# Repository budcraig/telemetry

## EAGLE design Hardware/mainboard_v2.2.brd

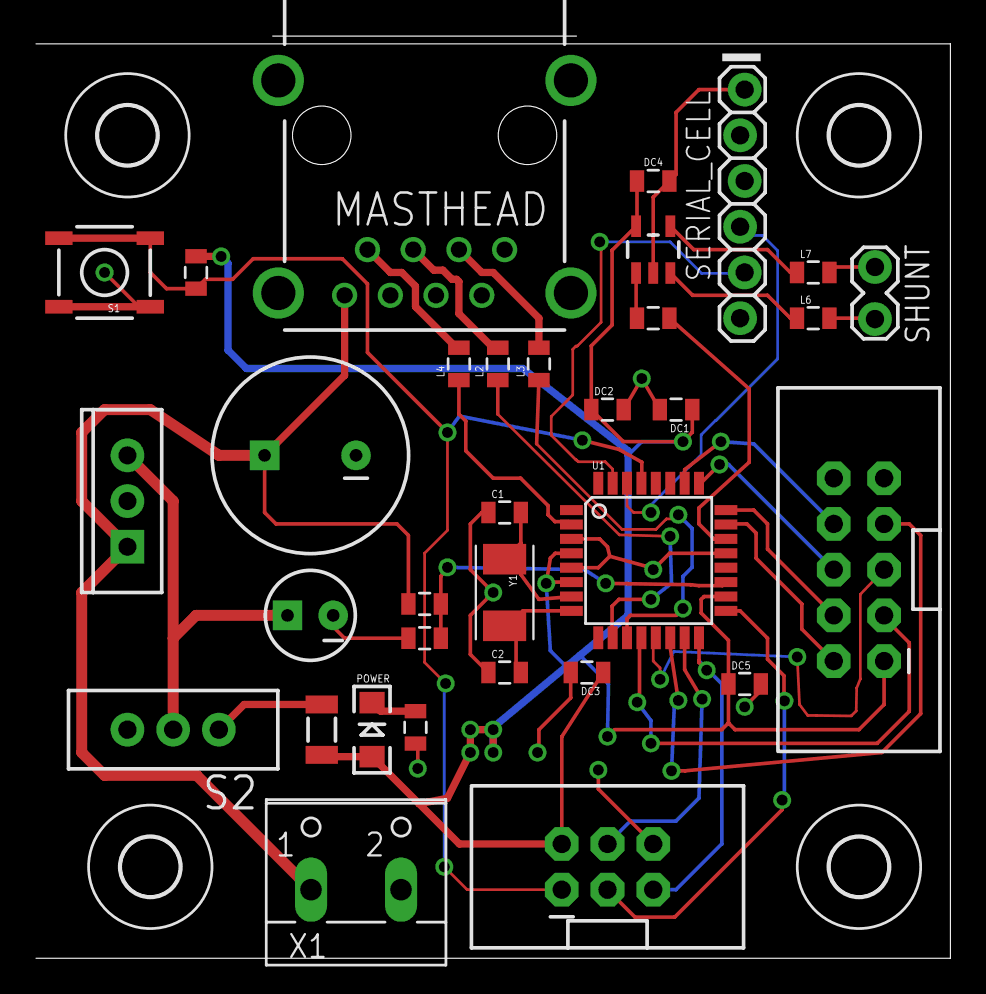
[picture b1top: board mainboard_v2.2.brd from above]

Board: 2 copper layers, 50.8 x 51.2 mm, 38 parts (1 on the bottom side), 34 nets.

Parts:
C1, C2: 22pF; 0805
C9: 100uF; CPOL-RADIAL-1000UF-25V
C10: 10uF; CPOL-RADIAL-10UF-25V
DC1, DC2, DC3, DC4, DC5: 0.1uF; 0805
H1, H2, H3, H4: MOUNT-HOLE3.2; 3,2
IC1: TO220-IGO
ICSP: 2X3-SHROUDED
L2, L3, L4, L6, L7: 0805
LCD: M05X2SHD_LOCK; 2X5-SHROUDED_LOCK
LOGO2: OSHW-LOGOL; OSHW-LOGO-L
MASTHEAD: RJ45-8L21-B; RJ45-SHIELD1
POWER: LED-1206
PTC: 750mA; PTC-1206
R1: 10kΩ; 0805
R2: 10kΩ 0.1%; 0805
R3: 1.2kΩ 0.1%; 0805
R4: 44.2kΩ 0.1%; 0805
R7: 56Ω; 0805
S1: TACTILE_SWITCH_SMD
S2: SWITCH-SPDT
SERIAL_CELL: 1X06_LOCK
SHUNT: 1X02_LOCK
U1: ATMEGA328P; TQFP32-08
U2: INA169; SOT23-5
X1: W237-102
Y1: CRYSTAL-TXC-7A

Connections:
3.3V: DC1.1, DC2.1, DC3.1, DC4.1, DC5.1, ICSP.2, LCD.1, POWER.A, PTC.2, R1.2, U1.4, U1.6, U1.18, U2.5
ANEM_CLK: L4.2, MASTHEAD.7
DIR_POT: L3.2, MASTHEAD.3
GND: C1.1, C2.1, C9.2, C10.2, DC1.2, DC2.2, DC3.2, DC4.2, DC5.2, IC1.GND, ICSP.6, LCD.9, MASTHEAD.1, MASTHEAD.2, MASTHEAD.4, MASTHEAD.6, R3.1, R7.1, S1.1, S1.2, SERIAL_CELL.1, U1.3, U1.5, U1.21, U2.2, X1.2
LCD_D4: LCD.2, U1.23
LCD_D5: LCD.4, U1.24
LCD_D6: LCD.6, U1.25
LCD_D7: LCD.8, U1.26
LCD_E: LCD.7, U1.14
LCD_RS: LCD.3, U1.12
LCD_RW: LCD.5, U1.13
MISO: ICSP.5, U1.16
MOSI: ICSP.4, U1.15
unnamed: PTC.1, S2.1
unnamed: L3.1, U1.11
unnamed: L2.1, U1.10
unnamed: L4.1, U1.2
unnamed: L6.1, U2.3
unnamed: L7.1, U2.4
unnamed: R4.2, U2.1
unnamed: POWER.C, R7.2
RESET: ICSP.1, R1.1, S1.3, S1.4, U1.29
SCK: ICSP.3, U1.17
SHIPS_BATTERY_VOLTAGE_ADC: R2.1, R3.2, U1.19
SHUNT: R4.1, U1.22
SHUNT+: L7.2, SHUNT.2
SHUNT-: L6.2, SHUNT.1
TEMP: L2.2, MASTHEAD.5
URX: SERIAL_CELL.4, U1.30
UTX: SERIAL_CELL.5, U1.31
VCC: C9.1, IC1.IN, MASTHEAD.8, R2.2, X1.1
VREG_OUT: C10.1, IC1.OUT, S2.2
XTAL1: C1.2, U1.7, Y1.P$2
XTAL2: C2.2, U1.8, Y1.P$1

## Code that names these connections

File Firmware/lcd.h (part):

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#define LCD_DATA1_PIN    1            /**< pin for 4bit data bit 1  */
#define LCD_DATA2_PIN    2            /**< pin for 4bit data bit 2  */
#define LCD_DATA3_PIN    3            /**< pin for 4bit data bit 3  */
#define LCD_RS_PORT      PORTB     /**< port for RS line         */
#define LCD_RS_PIN       0            /**< pin  for RS line         */
#define LCD_RW_PORT      PORTB     /**< port for RW line         */
#define LCD_RW_PIN       1            /**< pin  for RW line         */
#define LCD_E_PORT       PORTB     /**< port for Enable line     */
#define LCD_E_PIN        2            /**< pin  for Enable line     */

#elif defined(__AVR_AT90S4414__) || defined(__AVR_AT90S8515__) || defined(__AVR_ATmega64__) || \
      defined(__AVR_ATmega8515__)|| defined(__AVR_ATmega103__) || defined(__AVR_ATmega128__) || \
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
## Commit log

2013-09-18 schematic and board files, initial
2013-09-18 git files
2013-09-18 To-Do list updated on schematic
    +Add open source hardware logo to board silkscreen
2013-09-19 Organization
2013-09-21 initial commit of uart library
    uart library is a stupid hack, interrupt-driven isn't working at the
    moment.
2013-11-11 uart changed to interrupt based
    peter fleury's uart library
2013-12-23 v2.2 finale - boards ordered
2013-12-25 inital commit - masthead hardware solidworks models
2013-12-26 Added IGES - Wind Dir Sensor is balanced
2014-02-07 ADC to LCD, board to-do update
2014-02-09 ADC to volts conversion
2014-02-09 cleanup
2014-02-24 small change to wind dir hardware +windspeed code
2014-02-28 added code for ds18b20 on D7 (wind dir pin)
2014-03-03 ds18b20 mostly to interrupt, avoids 700ms busywait
2014-03-10 cellular callback output to LCD

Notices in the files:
parts and their libraries:
SparkFun-DigitalIC: Licensing: CC v3.0 Share-Alike You are welcome to use this library for commercial purposes.
